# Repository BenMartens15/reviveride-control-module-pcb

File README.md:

# ReviveRide: Modernizing Vintage Autos
### Project Overview
ReviveRide was developed as a capstone project for the Computer Engineering Technology program at Conestoga College. The goal of ReviveRide is to bring features found on modern vehicles to older vehicles. The project provides a dash camera, backup camera, head unit touchscreen with Android Auto, blind spot object detection, and remote start in an all-in-one, easy to install kit.

### Control Module
The control module is responsible for providing power to every component in the system when the car is turned on. It is also responsible for receiving the remote start signal from the key fob and switching voltages to the ignition system to start the car.

This repo contains the schematic and PCB for the control module. The firmware for the control module can be found here: https://github.com/BenMartens15/reviveride-control-module-firmware

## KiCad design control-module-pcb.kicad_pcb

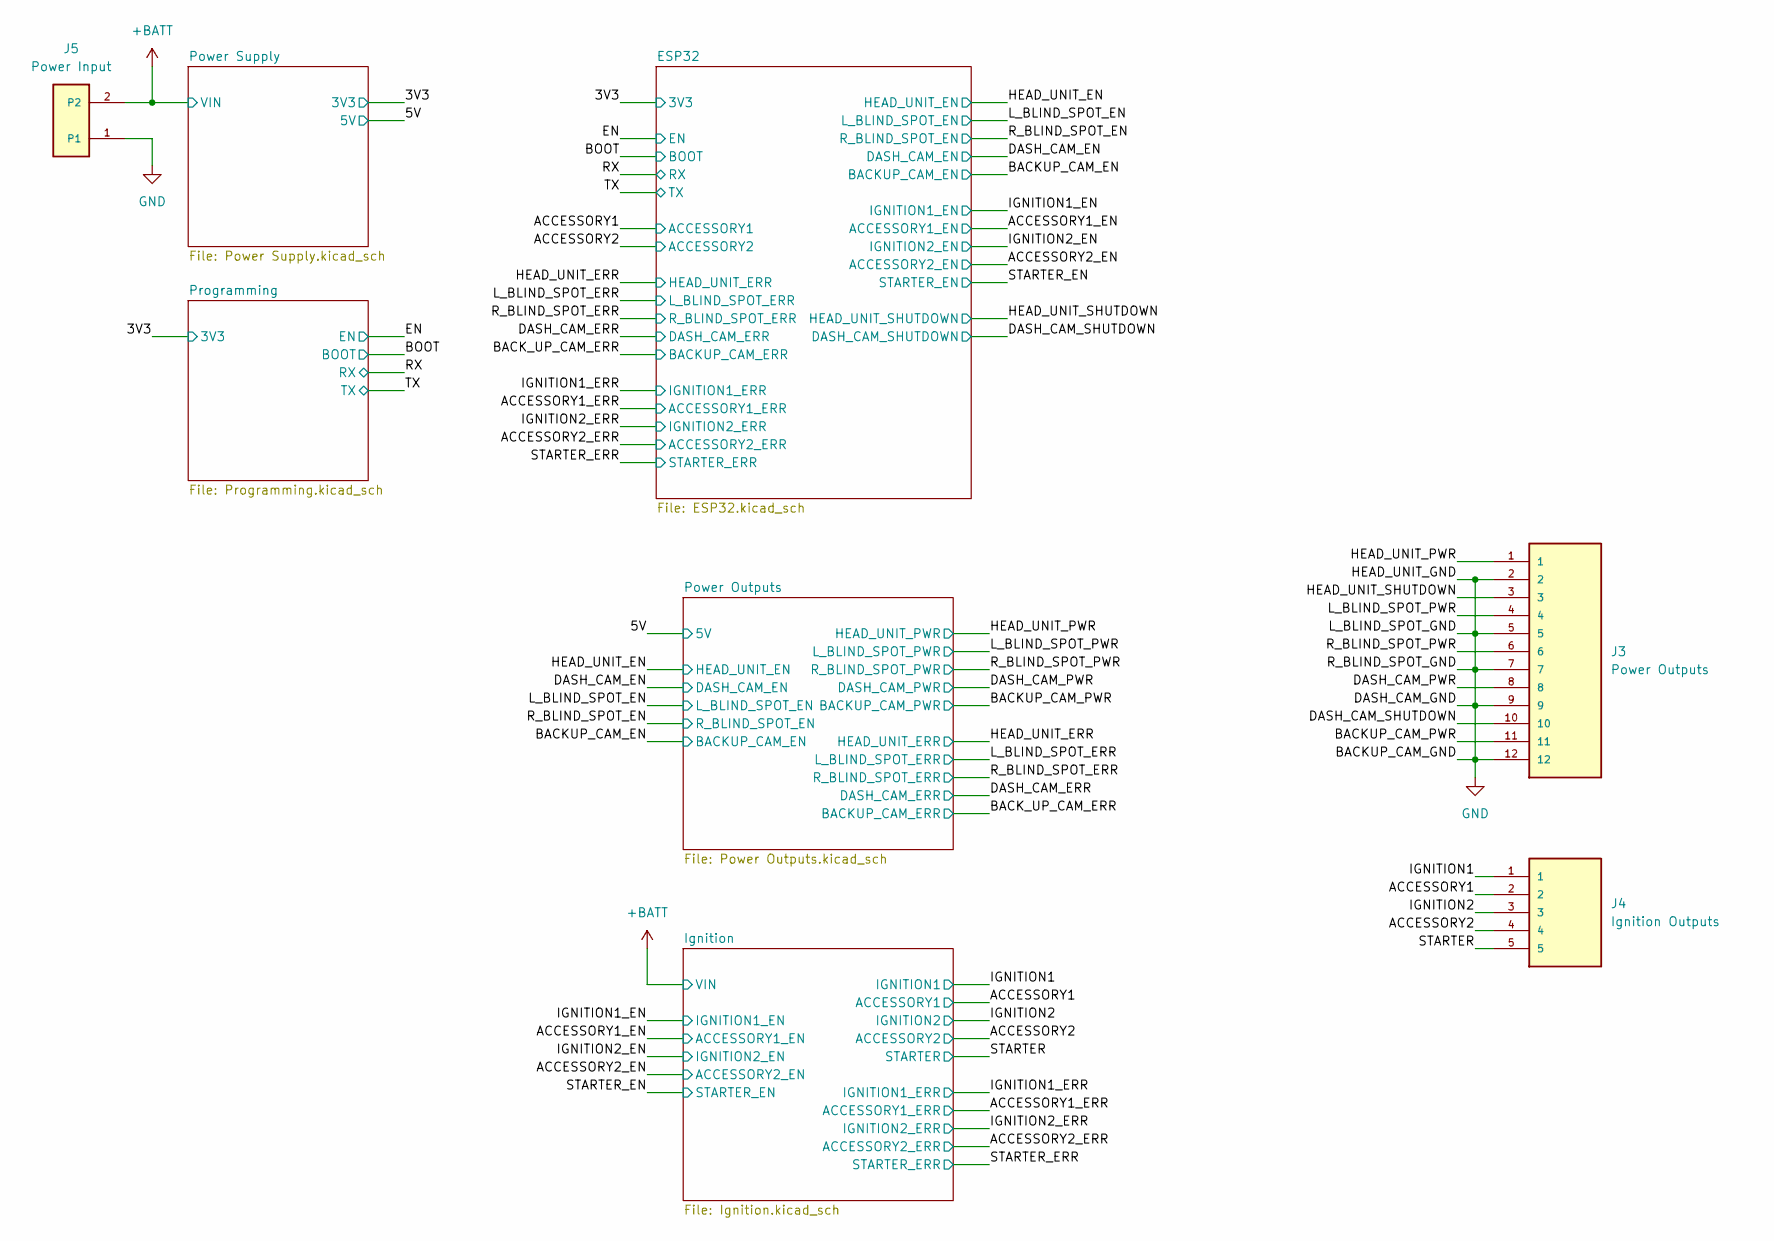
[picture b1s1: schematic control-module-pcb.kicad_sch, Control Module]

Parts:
J3: Power Outputs; TE_1-1776275-2; PARTREV R
J4: Ignition Outputs; TE_1776275-5; PARTREV R
J5: Power Input; TE_1776275-2; VOLTAGE_RATING_AC 250V; PART_DESCRIPTION TERM BLOCK 2POS SIDE ENT 3.5MM

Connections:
/ACCESSORY1: J4.2; also elsewhere on the board
/ACCESSORY2: J4.4; also elsewhere on the board
/BACKUP_CAM_PWR: J3.11; also elsewhere on the board
/DASH_CAM_PWR: J3.8; also elsewhere on the board
/DASH_CAM_SHUTDOWN: J3.10; also elsewhere on the board
/HEAD_UNIT_PWR: J3.1; also elsewhere on the board
/HEAD_UNIT_SHUTDOWN: J3.3; also elsewhere on the board
/IGNITION2: J4.3; also elsewhere on the board
/L_BLIND_SPOT_PWR: J3.4; also elsewhere on the board
/R_BLIND_SPOT_PWR: J3.6; also elsewhere on the board
/STARTER: J4.5; also elsewhere on the board
GND: J3.2, J3.5, J3.7, J3.9, J3.12, J5.1; also elsewhere on the board

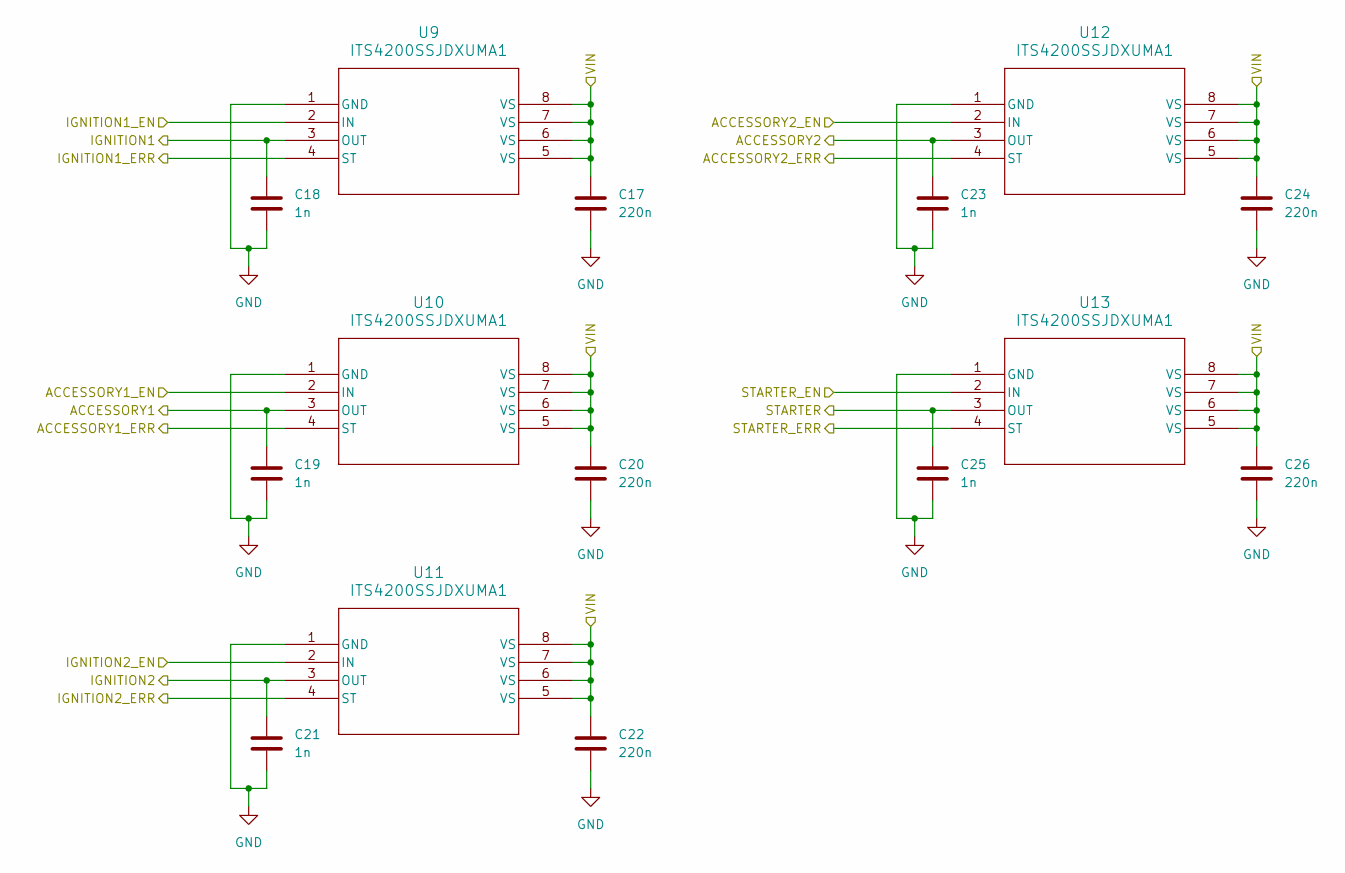
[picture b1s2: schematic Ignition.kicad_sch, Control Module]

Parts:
C17, C20, C22, C24, C26: 220n
C18, C19, C21, C23, C25: 1n
U9, U10, U11, U12, U13: ITS4200SSJDXUMA1; PG-DSO-8-24_INF

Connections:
/ACCESSORY1: C19.2, U10.3 (OUT); also elsewhere on the board
/ACCESSORY1_EN: U10.2 (IN); also elsewhere on the board
/ACCESSORY1_ERR: U10.4 (ST); also elsewhere on the board
/ACCESSORY2: C23.2, U12.3 (OUT); also elsewhere on the board
/ACCESSORY2_EN: U12.2 (IN); also elsewhere on the board
/ACCESSORY2_ERR: U12.4 (ST); also elsewhere on the board
/IGNITION1_EN: U9.2 (IN); also elsewhere on the board
/IGNITION1_ERR: U9.4 (ST); also elsewhere on the board
/IGNITION2: C21.2, U11.3 (OUT); also elsewhere on the board
/IGNITION2_EN: U11.2 (IN); also elsewhere on the board
/IGNITION2_ERR: U11.4 (ST); also elsewhere on the board
/STARTER: C25.2, U13.3 (OUT); also elsewhere on the board
/STARTER_EN: U13.2 (IN); also elsewhere on the board
/STARTER_ERR: U13.4 (ST); also elsewhere on the board
GND: C17.1, C18.1, C19.1, C20.1, C21.1, C22.1, C23.1, C24.1, C25.1, C26.1, U9.1 (GND), U10.1 (GND), U11.1 (GND), U12.1 (GND), U13.1 (GND); also elsewhere on the board

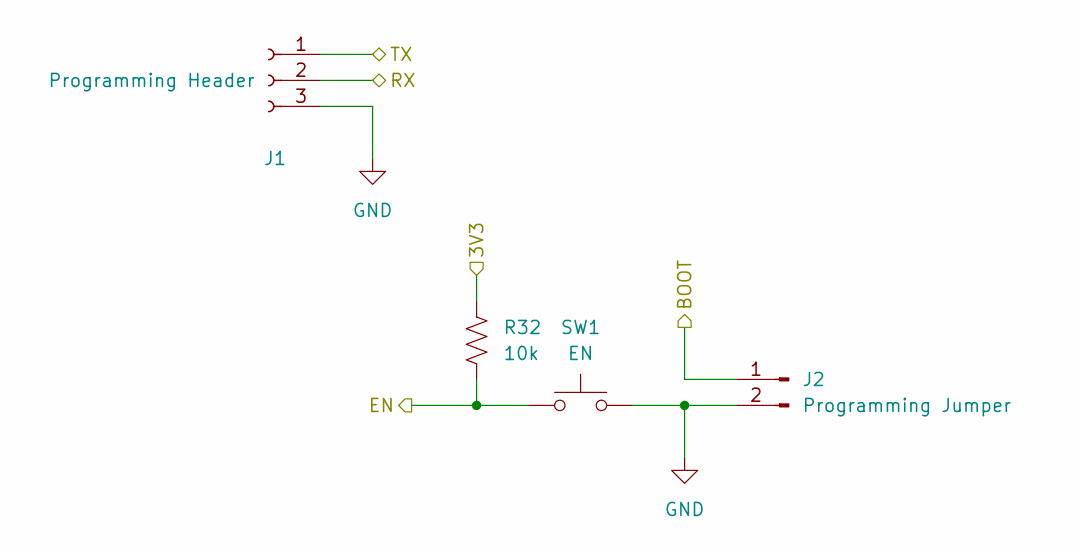
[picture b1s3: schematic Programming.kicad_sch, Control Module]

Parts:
J1: Programming Header; PinHeader_1x03_P2.54mm_Horizontal
J2: Programming Jumper; PinHeader_1x02_P2.54mm_Horizontal
R32: 10k; R_0603_1608Metric
SW1: EN; SW_SPST_TL3305B

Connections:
/BOOT: J2.1; also elsewhere on the board
/EN: R32.2, SW1.2; also elsewhere on the board
/RX: J1.2; also elsewhere on the board
/TX: J1.1; also elsewhere on the board
GND: J1.3, J2.2, SW1.1; also elsewhere on the board

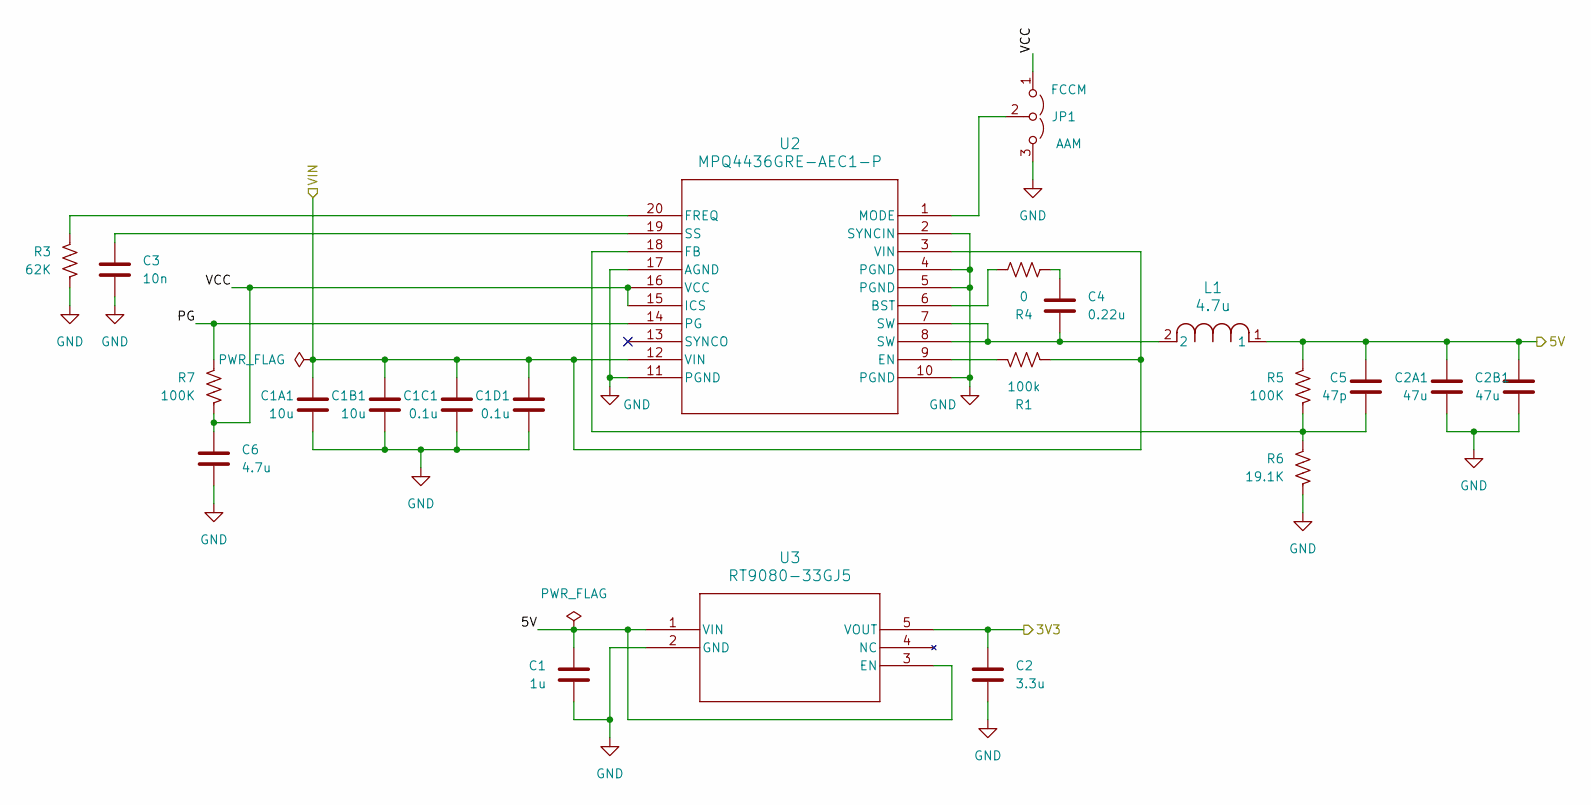
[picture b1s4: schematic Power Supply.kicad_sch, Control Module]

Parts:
C1: 1u; C_0603_1608Metric
C1A1, C1B1: 10u; C_1206_3216Metric
C1C1, C1D1: 0.1u; C_0603_1608Metric
C2: 3.3u; C_0603_1608Metric
C2A1, C2B1: 47u; C_1206_3216Metric
C3: 10n; C_0603_1608Metric
C4: 0.22u; C_0603_1608Metric
C5: 47p; C_0603_1608Metric
C6: 4.7u; C_0603_1608Metric
JP1: PinHeader_1x03_P2.54mm_Vertical
L1: 4.7u; IND_PA4342_PUL
R1: 100k; R_0603_1608Metric
R3: 62K; R_0603_1608Metric
R4: 0; R_0603_1608Metric
R5, R7: 100K; R_0603_1608Metric
R6: 19.1K; R_0603_1608Metric
U2: MPQ4436GRE-AEC1-P; QFN-4x4_MPQ4436-AEC1_MNP
U3: RT9080-33GJ5; TSOT-23-5_RIT

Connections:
/3V3: C2.1, U3.5 (VOUT); also elsewhere on the board
/5V: C1.1, C2A1.1, C2B1.1, C5.1, L1.1, R5.1, U3.1 (VIN), U3.3 (EN); also elsewhere on the board
/Power Supply/PG: R7.1, U2.14 (PG)
/Power Supply/VCC: C6.1, JP1.1 (A), R7.2, U2.15 (ICS), U2.16 (VCC)
GND: C1.2, C1A1.2, C1B1.2, C1C1.2, C1D1.2, C2.2, C2A1.2, C2B1.2, C3.2, C6.2, JP1.3 (B), R3.2, R6.2, U2.2 (SYNCIN), U2.4 (PGND), U2.5 (PGND), U2.10 (PGND), U2.11 (PGND), U2.17 (AGND), U3.2 (GND); also elsewhere on the board
unnamed: C4.1, L1.2, U2.7 (SW), U2.8 (SW)
unnamed: C4.2, R4.1
unnamed: JP1.2 (C), U2.1 (MODE)
unnamed: R4.2, U2.6 (BST)
unnamed: R1.1, U2.9 (EN)
unnamed: C5.2, R5.2, R6.1, U2.18 (FB)
unnamed: R3.1, U2.20 (FREQ)
unnamed: C3.1, U2.19 (SS)

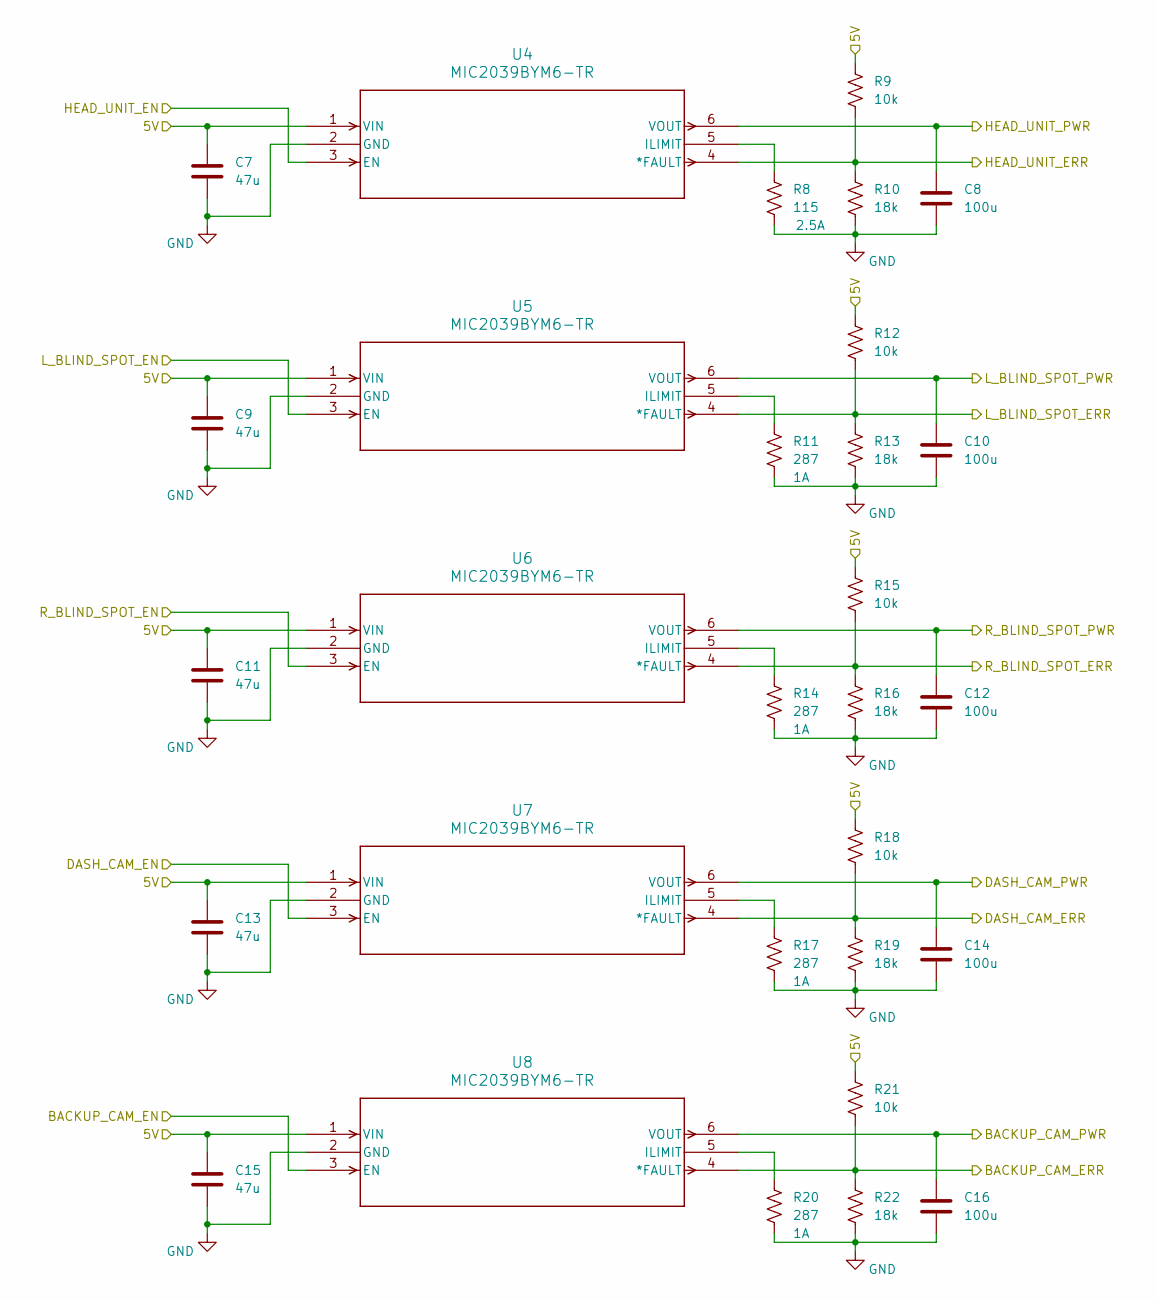
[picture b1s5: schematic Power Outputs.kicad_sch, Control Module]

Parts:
C7, C9, C11, C13, C15: 47u; C_1206_3216Metric
C8, C10, C12, C14, C16: 100u; C_1206_3216Metric
R8: 115; R_0603_1608Metric
R9, R12, R15, R18, R21: 10k; R_0603_1608Metric
R10, R13, R16, R19, R22: 18k; R_0603_1608Metric
R11, R14, R17, R20: 287; R_0603_1608Metric
U4, U5, U6, U7, U8: MIC2039BYM6-TR; SOT-23-6_M6_MCH

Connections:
/5V: C7.1, C9.1, C11.1, C13.1, C15.1, R9.1, R12.1, R15.1, R18.1, R21.1, U4.1 (VIN), U5.1 (VIN), U6.1 (VIN), U7.1 (VIN), U8.1 (VIN); also elsewhere on the board
/BACKUP_CAM_EN: U8.3 (EN); also elsewhere on the board
/BACKUP_CAM_PWR: C16.1, U8.6 (VOUT); also elsewhere on the board
/BACK_UP_CAM_ERR: R21.2, R22.1, U8.4 (*FAULT); also elsewhere on the board
/DASH_CAM_EN: U7.3 (EN); also elsewhere on the board
/DASH_CAM_ERR: R18.2, R19.1, U7.4 (*FAULT); also elsewhere on the board
/DASH_CAM_PWR: C14.1, U7.6 (VOUT); also elsewhere on the board
/HEAD_UNIT_EN: U4.3 (EN); also elsewhere on the board
/HEAD_UNIT_ERR: R9.2, R10.1, U4.4 (*FAULT); also elsewhere on the board
/HEAD_UNIT_PWR: C8.1, U4.6 (VOUT); also elsewhere on the board
/L_BLIND_SPOT_EN: U5.3 (EN); also elsewhere on the board
/L_BLIND_SPOT_ERR: R12.2, R13.1, U5.4 (*FAULT); also elsewhere on the board
/L_BLIND_SPOT_PWR: C10.1, U5.6 (VOUT); also elsewhere on the board
/R_BLIND_SPOT_EN: U6.3 (EN); also elsewhere on the board
/R_BLIND_SPOT_ERR: R15.2, R16.1, U6.4 (*FAULT); also elsewhere on the board
/R_BLIND_SPOT_PWR: C12.1, U6.6 (VOUT); also elsewhere on the board
GND: C7.2, C8.2, C9.2, C10.2, C11.2, C12.2, C13.2, C14.2, C15.2, C16.2, R8.2, R10.2, R11.2, R13.2, R14.2, R16.2, R17.2, R19.2, R20.2, R22.2, U4.2 (GND), U5.2 (GND), U6.2 (GND), U7.2 (GND), U8.2 (GND); also elsewhere on the board
unnamed: R8.1, U4.5 (ILIMIT)
unnamed: R11.1, U5.5 (ILIMIT)
unnamed: R14.1, U6.5 (ILIMIT)
unnamed: R17.1, U7.5 (ILIMIT)
unnamed: R20.1, U8.5 (ILIMIT)

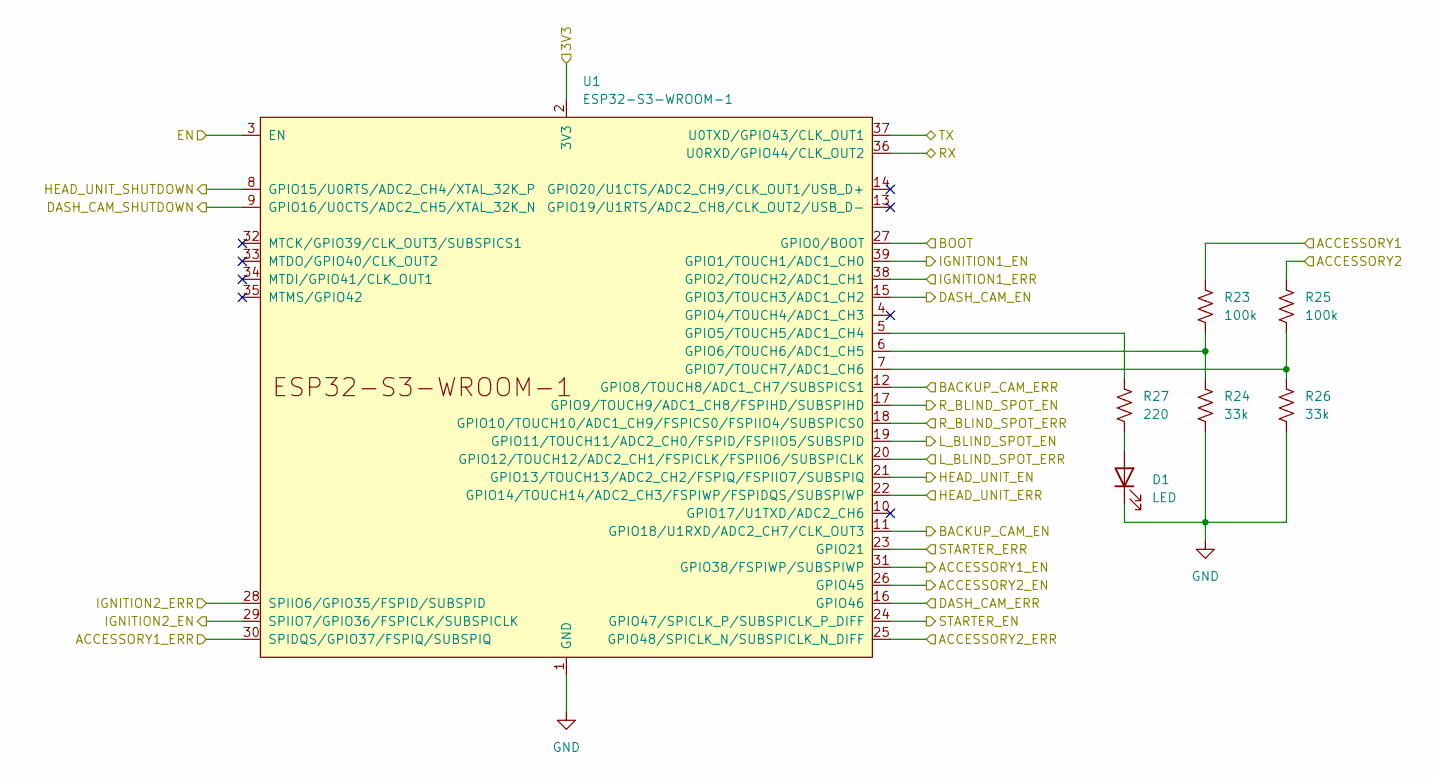
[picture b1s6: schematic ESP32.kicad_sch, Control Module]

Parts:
D1: LED; LED_0603_1608Metric
R23, R25: 100k; R_0603_1608Metric
R24, R26: 33k; R_0603_1608Metric
R27: 220; R_0603_1608Metric
U1: ESP32-S3-WROOM-1

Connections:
/3V3: U1.2 (3V3); also elsewhere on the board
/ACCESSORY1: R23.1; also elsewhere on the board
/ACCESSORY1_EN: U1.31 (GPIO38/FSPIWP/SUBSPIWP); also elsewhere on the board
/ACCESSORY1_ERR: U1.30 (SPIDQS/GPIO37/FSPIQ/SUBSPIQ); also elsewhere on the board
/ACCESSORY2: R25.1; also elsewhere on the board
/ACCESSORY2_EN: U1.26 (GPIO45); also elsewhere on the board
/ACCESSORY2_ERR: U1.25 (GPIO48/SPICLK_N/SUBSPICLK_N_DIFF); also elsewhere on the board
/BACKUP_CAM_EN: U1.11 (GPIO18/U1RXD/ADC2_CH7/CLK_OUT3); also elsewhere on the board
/BACK_UP_CAM_ERR: U1.12 (GPIO8/TOUCH8/ADC1_CH7/SUBSPICS1); also elsewhere on the board
/BOOT: U1.27 (GPIO0/BOOT); also elsewhere on the board
/DASH_CAM_EN: U1.15 (GPIO3/TOUCH3/ADC1_CH2); also elsewhere on the board
/DASH_CAM_ERR: U1.16 (GPIO46); also elsewhere on the board
/DASH_CAM_SHUTDOWN: U1.9 (GPIO16/U0CTS/ADC2_CH5/XTAL_32K_N); also elsewhere on the board
/EN: U1.3 (EN); also elsewhere on the board
/HEAD_UNIT_EN: U1.21 (GPIO13/TOUCH13/ADC2_CH2/FSPIQ/FSPIIO7/S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); also elsewhere on the board
/HEAD_UNIT_ERR: U1.22 (GPIO14/TOUCH14/ADC2_CH3/FSPIWP/FSPIDQS/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); also elsewhere on the board
/HEAD_UNIT_SHUTDOWN: U1.8 (GPIO15/U0RTS/ADC2_CH4/XTAL_32K_P); also elsewhere on the board
/IGNITION1_EN: U1.39 (GPIO1/TOUCH1/ADC1_CH0); also elsewhere on the board
/IGNITION1_ERR: U1.38 (GPIO2/TOUCH2/ADC1_CH1); also elsewhere on the board
/IGNITION2_EN: U1.29 (SPIIO7/GPIO36/FSPICLK/SUBSPICLK); also elsewhere on the board
/IGNITION2_ERR: U1.28 (SPIIO6/GPIO35/FSPID/SUBSPID); also elsewhere on the board
/L_BLIND_SPOT_EN: U1.19 (GPIO11/TOUCH11/ADC2_CH0/FSPID/FSPIIO5/S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); also elsewhere on the board
/L_BLIND_SPOT_ERR: U1.20 (GPIO12/TOUCH12/ADC2_CH1/FSPICLK/FSPIIO6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); also elsewhere on the board
/RX: U1.36 (U0RXD/GPIO44/CLK_OUT2); also elsewhere on the board
/R_BLIND_SPOT_EN: U1.17 (GPIO9/TOUCH9/ADC1_CH8/FSPIHD/SUBSPIHD); also elsewhere on the board
/R_BLIND_SPOT_ERR: U1.18 (GPIO10/TOUCH10/ADC1_CH9/FSPICS0/FSPIIO4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); also elsewhere on the board
/STARTER_EN: U1.24 (GPIO47/SPICLK_P/SUBSPICLK_P_DIFF); also elsewhere on the board
/STARTER_ERR: U1.23 (GPIO21); also elsewhere on the board
/TX: U1.37 (U0TXD/GPIO43/CLK_OUT1); also elsewhere on the board
GND: D1.1 (K), R24.2, R26.2, U1.1 (GND), U1.40 (GND), U1.41 (GND); also elsewhere on the board
unnamed: D1.2 (A), R27.2
unnamed: R27.1, U1.5 (GPIO5/TOUCH5/ADC1_CH4)
unnamed: R23.2, R24.1, U1.6 (GPIO6/TOUCH6/ADC1_CH5)
unnamed: R25.2, R26.1, U1.7 (GPIO7/TOUCH7/ADC1_CH6)

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
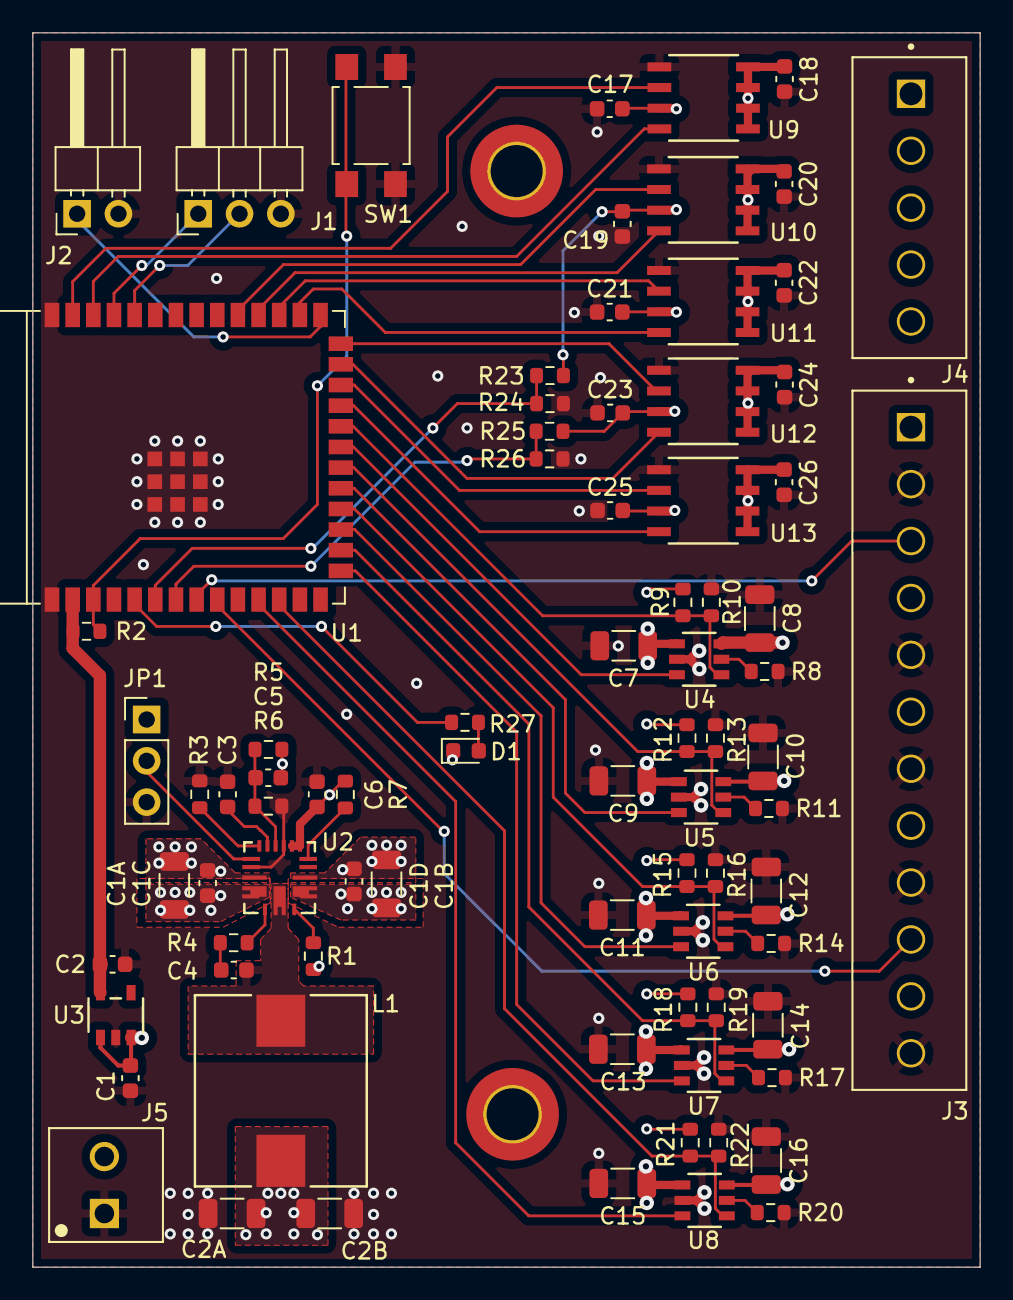
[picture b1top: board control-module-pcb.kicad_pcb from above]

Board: 4 copper layers, 58.2 x 75.9 mm, 81 parts (0 on the bottom side), 59 nets.

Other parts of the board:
C1A, C1B: 10u; C_1206_3216Metric
C1C, C1D: 0.1u; C_0603_1608Metric
C2A, C2B: 47u; C_1206_3216Metric
R2: 10k; R_0603_1608Metric

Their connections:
/3V3: R2.1; also elsewhere on the board
/5V: C2A.1, C2B.1; also elsewhere on the board
/EN: R2.2; also elsewhere on the board
GND: C1A.2, C1B.2, C1C.2, C1D.2, C2A.2, C2B.2; also elsewhere on the board

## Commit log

2023-11-09 created KiCAD project and added PMIC chip library
2023-11-22 hierarchical sheets and connections done
2023-11-22 power supply circuit schematic done
2023-11-23 working on ignition and power output sheets
2023-11-23 assign ESP32 pins
2024-01-24 switch Ignition page to use load drivers rather than discrete FETs
2024-02-01 fix ERC errors
2024-02-06 Assigning footprints
2024-02-08 finished assigning footprints and started PCB layout
2024-02-08 layout mostly complete
2024-02-09 made a few adjustments and generated gerbers
2024-02-09 add LED for debugging
2024-02-09 a few silk screen updates
2024-02-13 add 3d models and export step
2024-02-14 removed blind via from PCB
